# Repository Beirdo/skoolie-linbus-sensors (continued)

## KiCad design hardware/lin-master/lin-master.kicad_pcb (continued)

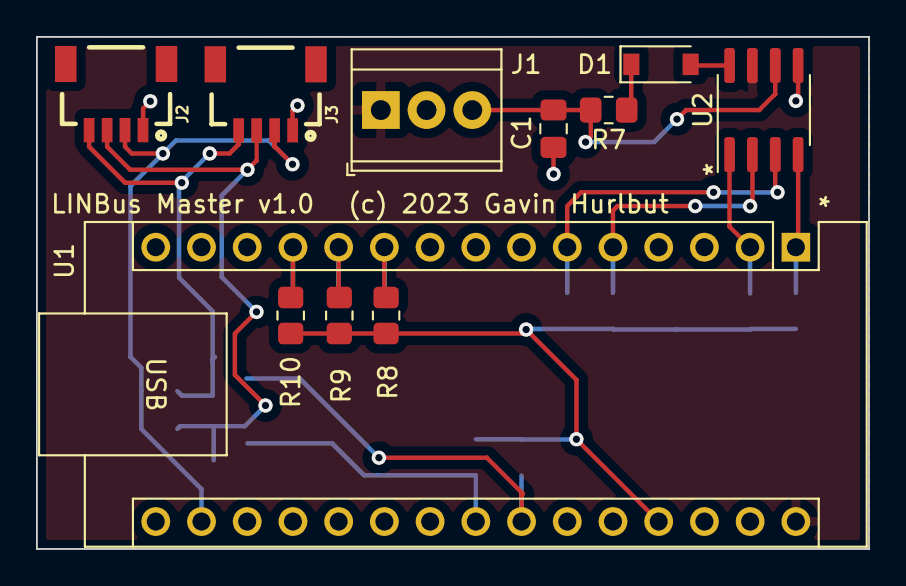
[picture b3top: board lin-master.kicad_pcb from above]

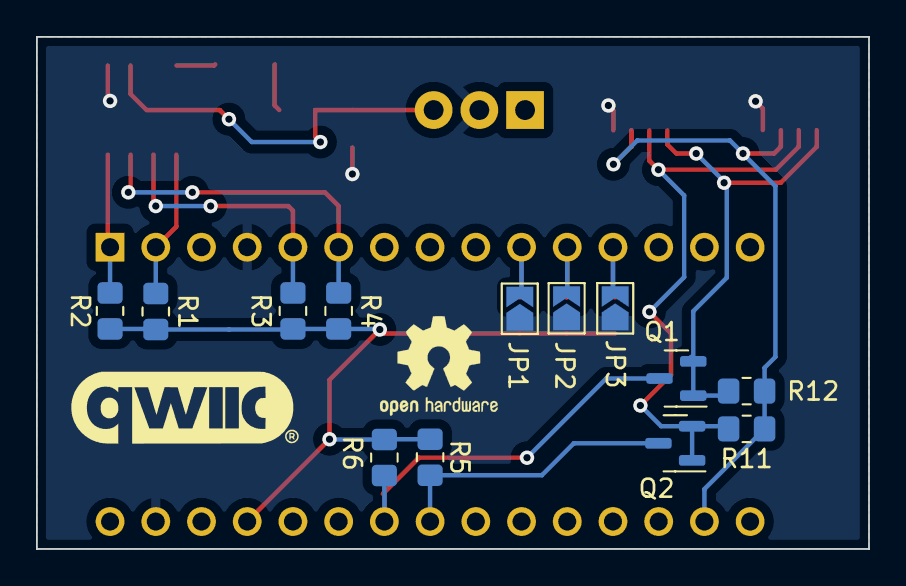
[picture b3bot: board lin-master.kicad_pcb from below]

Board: 2 copper layers, 46.2 x 28.4 mm, 24 parts (13 on the bottom side), 18 nets.

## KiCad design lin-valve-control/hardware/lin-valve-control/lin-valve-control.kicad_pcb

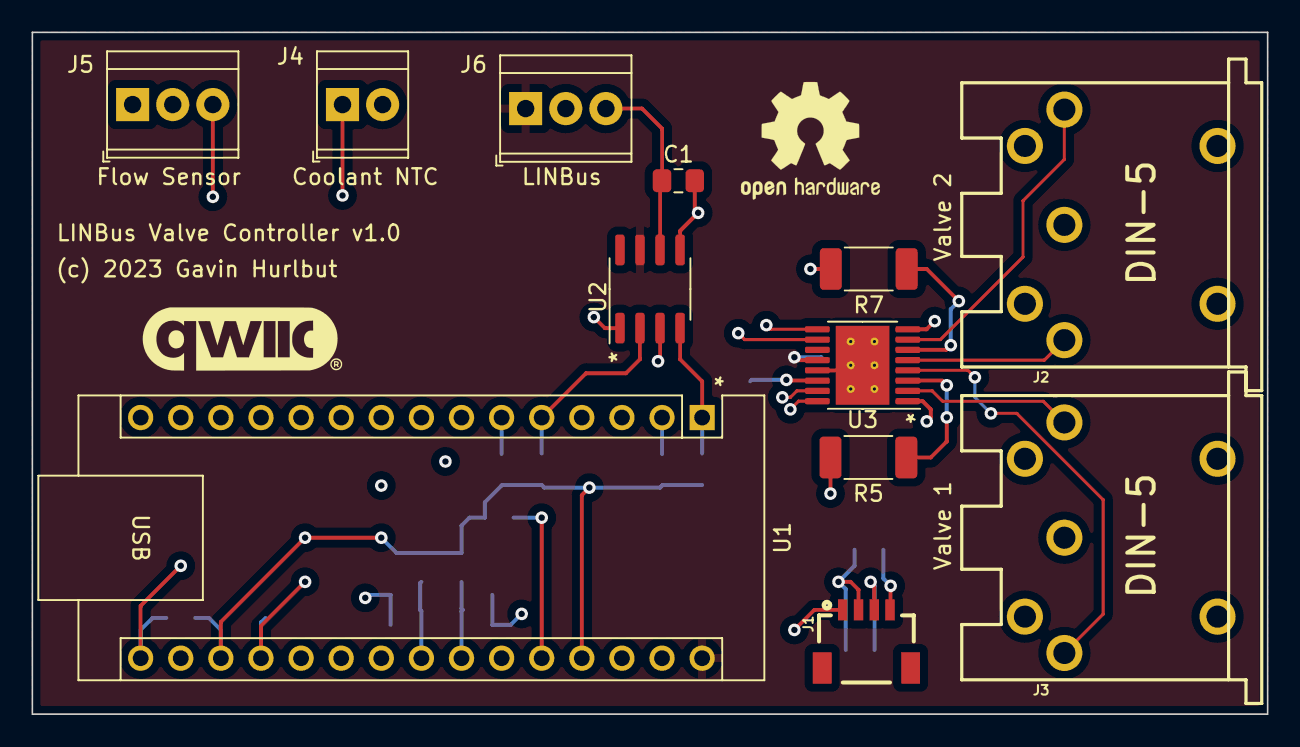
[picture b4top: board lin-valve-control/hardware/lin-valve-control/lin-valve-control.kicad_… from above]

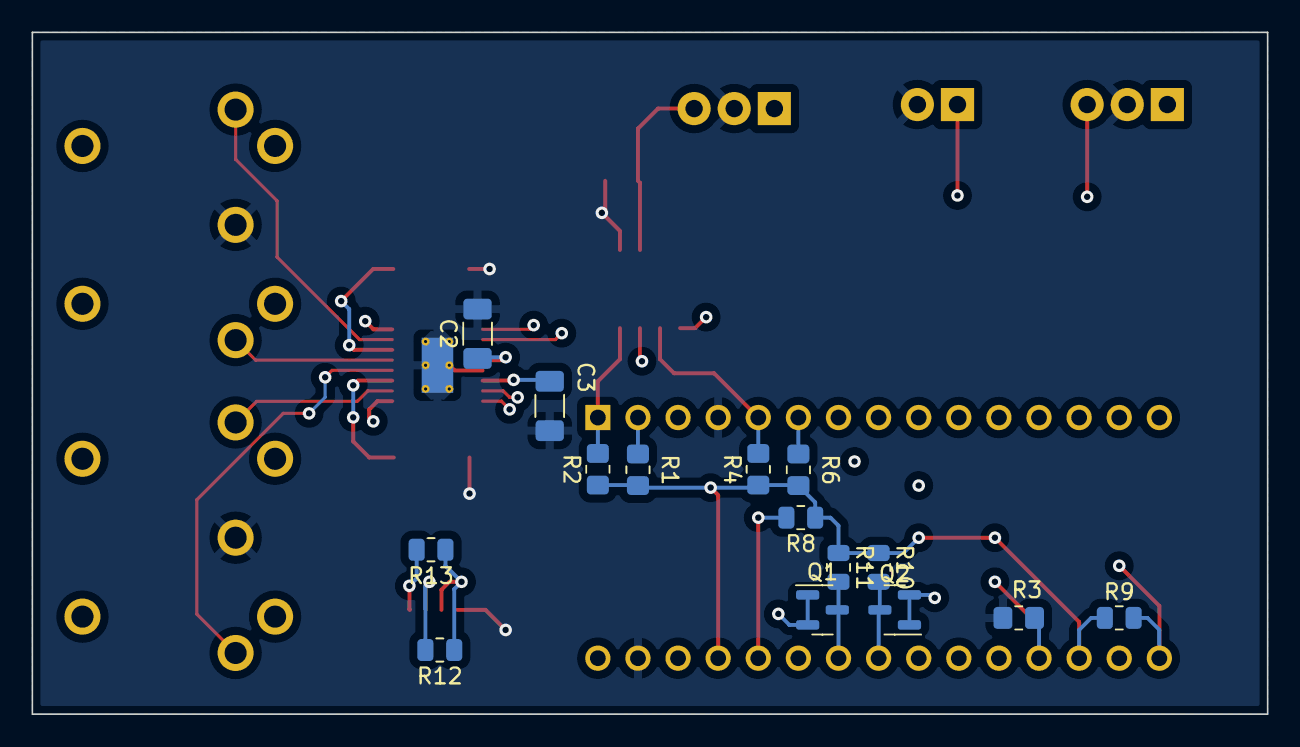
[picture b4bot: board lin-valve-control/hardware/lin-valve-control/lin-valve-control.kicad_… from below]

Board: 4 copper layers, 78.2 x 43.2 mm, 27 parts (15 on the bottom side), 32 nets.

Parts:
C1: 220pF; C_0805_2012Metric_Pad1.18x1.45mm_HandSolder
C2: 10uF 16V; C_1206_3216Metric_Pad1.33x1.80mm_HandSolder
C3: 2.2uF 6.3V; C_1206_3216Metric_Pad1.33x1.80mm_HandSolder
J1: QWIIC Connector; 1X04_1MM_RA
J2, J3: DIN-5_180degree; DIN5-RA-PTH
J4: Screw_Terminal_01x02; TerminalBlock_TE_282834-2_1x02_P2.54mm_Horizontal
J5, J6: Screw_Terminal_01x03; TerminalBlock_TE_282834-3_1x03_P2.54mm_Horizontal
Q1, Q2: 2N7002; SOT-23
R1, R2, R3, R4, R6: 10k; R_0805_2012Metric_Pad1.20x1.40mm_HandSolder
R5, R7: 2R 2W; R_2010_5025Metric_Pad1.40x2.65mm_HandSolder
R8, R9, R10, R11, R12, R13: 10k; R_0805_2012Metric
U1: Arduino_Nano_v3.x; Arduino_Nano
U2: TJA1021T; SOIC-8_3.9x4.9mm_P1.27mm
U3: DRV8833PWP; HTSSOP-16-1EP_4.4x5mm_P0.65mm_EP3.4x5mm_Mask2.46x2.31mm_The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

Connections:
+3V3: J1.2 (VCC), R12.1, R13.1, U1.17 (3V3)
+5V: J5.1, R1.1, R2.1, R4.1, R6.1, R8.1, R9.1, R10.1, R11.1, U1.18 (AREF), U1.27 (+5V)
+12V: C2.1, J6.1, U1.30 (VIN), U2.7 (VBAT), U3.12 (VM)
COOLANT_NTC: J4.1, R8.2, U1.26 (A7)
FLOW_PULSE: J5.3, U1.11 (D8)
GND: C1.2, C2.2, C3.2, J1.1 (GND), J2.2, J3.2, J4.2, J5.2, J6.2, R3.2, R5.2, R7.2, U1.4 (GND), U1.29 (GND), U2.5 (GND), U3.13 (GND), U3.17 (GND(PPAD))
LIN: C1.1, J6.3, U2.6 (LIN)
MOTOR_EN: R3.1, U1.19 (A0), U3.1 (nSLEEP)
unnamed: C3.1, U3.14 (VINT)
unnamed: R5.1, U3.3 (AISEN)
unnamed: R7.1, U3.6 (BISEN)
RXD: R1.2, U1.2 (D0/RX), U2.1 (RXD)
SCL: J1.4 (SCL), Q1.1 (G), Q1.2 (S), R13.2
SCL5: Q1.3 (D), R11.2, U1.24 (A5)
SDA: J1.3 (SDA), Q2.1 (G), Q2.2 (S), R12.2
SDA5: Q2.3 (D), R10.2, U1.23 (A4)
TXD: R2.2, U1.1 (D1/TX), U2.4 (TXD)
VALVE1+: J3.1, U3.2 (AOUT1)
VALVE1-: J3.3, U3.4 (AOUT2)
VALVE1_CLOSED: J3.5, U1.9 (D6)
VALVE1_OPEN: J3.4, U1.10 (D7)
VALVE2+: J2.1, U3.7 (BOUT1)
VALVE2-: J2.3, U3.5 (BOUT2)
VALVE2_CLOSED: J2.5, U1.14 (D11)
VALVE2_OPEN: J2.4, U1.15 (D12)
VALVE_IN1+: U1.7 (D4), U3.16 (AIN1)
VALVE_IN1-: U1.8 (D5), U3.15 (AIN2)
VALVE_IN2+: U1.12 (D9), U3.9 (BIN1)
VALVE_IN2-: U1.13 (D10), U3.10 (BIN2)
~LIN_SLP: R4.2, U1.5 (D2), U2.2 (~SLP)
~LIN_WAKE: R6.2, U1.6 (D3), U2.3 (~WAKE)
~MOTOR_FAULT: R9.2, U1.16 (D13), U3.8 (nFAULT)

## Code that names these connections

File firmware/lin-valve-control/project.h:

#ifndef __project_h_
#define __project_h_

#include <Arduino.h>
#include <Beirdo-Utilities.h>
#include <TCA9534-GPIO.h>

#define PIN_SCL           PIN_PB0
#define PIN_SDA           PIN_PB1
#define PIN_TXD           PIN_PB2
#define PIN_RXD           PIN_PB3
#define PIN_UPDI          PIN_PA0
#define PIN_VPROPI        PIN_PA1
#define PIN_I2C_INT       PIN_PA2
#define PIN_RESET         PIN_PA3
#define PIN_PHASE_PWM     PIN_PA4
#define PIN_LIN_SLP       PIN_PA5
#define PIN_LIN_WAKE      PIN_PA6
#define PIN_LED           PIN_PA7

// On the TCA9534
#define PIN_ENABLE        0
#define PIN_SLEEP         1
#define PIN_VALVE_CLOSED  4
#define PIN_VALVE_OPENED  5
#define PIN_FAULT         6

#define VALVE_CLOSED      BIT(3)
#define VALVE_OPENED      BIT(2)
#define VALVE_CLOSE       BIT(1)
#define VALVE_OPEN        BIT(0)

#define I2C_ADDR0_LCD     0x27
#define I2C_ADDR1_LCD     0x3F
#define I2C_ADDR_TCA9534  0x20

void setPhasePWM(bool cw, bool ccw);

extern TCA9534 tca9534;

#endif

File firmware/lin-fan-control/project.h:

#ifndef __project_h_
#define __project_h_

#include <Arduino.h>
#include <Beirdo-Utilities.h>

#define PIN_SCL           PIN_PB0
#define PIN_SDA           PIN_PB1
#define PIN_TXD           PIN_PB2
#define PIN_RXD           PIN_PB3
#define PIN_UPDI          PIN_PA0
#define PIN_ALERT         PIN_PA1
#define PIN_TCRIT         PIN_PA2
#define PIN_RESET         PIN_PA3
#define PIN_LIN_SLP       PIN_PA4
#define PIN_LIN_WAKE      PIN_PA5
#define PIN_LED           PIN_PA7

#endif

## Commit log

2023-02-04 Import some old stuff before its lost
2023-02-04 Redo the valve controller using an Arduino Nano
2023-02-04 Added LINBus Master schematic/layout
2023-02-04 Move flow sensor to ICP1, run it at 5V
2023-02-04 Move the hardware designs under hardware/
2023-02-05 Added firmware v1 for the valve-control board
2023-02-05 Add library
2023-02-05 Added I2C Addr lines and level translation
2023-02-06 Added firmware for lin-master
    - also added I2C address selection, and built-in 3.3V->5V translation
    and a second QWIIC connector.
2023-02-10 Added pins to control the cooling fan and the cooling pump
2023-02-10 Plumbed in the PWM Fan control and pump control
2023-02-10 Put in the Coolant Pump and Cooling Fan bits
2023-02-10 Sigh. forgot to save.
2023-02-15 Splitting into multiple pages.
2023-02-15 Update lin-master firmware and valve control board
2023-02-15 Updated valve controller board
2023-02-15 Add a connector to attach 20x4 LCD on an I2C backpack
2023-02-15 Regenerate schematic PDF
2023-02-15 Seems I have to *plot* this schematic, not print.
    - if I use print, it will only do either the title block OR the
    circuitry, but if I plot it works.
2023-02-17 Change to A4 size paper
2023-02-17 Completely redo the valve controller. One valve only.
2023-02-17 Uptdate title block
2023-02-17 Update firmware readme
2023-02-17 Add PCA9536 for the LINBus Address
2023-02-18 Get this in place (barely) on ATTiny824.
    - should not be THAT big, I thought. Investigation to follow:
    Sketch uses 7998 bytes (97%) of program storage space. Maximum is 8192 bytes.
2023-02-18 Make things less dynamic
    Sketch uses 7687 bytes (93%) of program storage space. Maximum is 8192 bytes.
2023-02-18 Board design for coolant temperature thermistors.
2023-02-18 Add firmware for lin-coolant-temperature, cleanup layout
2023-02-18 Add lin-flow-sensor hardware and preliminary firmware
2023-02-19 Add fan control hardware design.
    - control one fan with 2, 3 or 4 pin connectivity, providing PWM and tach support for all.
    - one remote PN-junction temperature probe (will put in the outbound air flow)
2023-02-19 Adding shell firmware forthe fan control
2023-02-19 Started mapping out registers
2023-02-20 AddingLM96163 support
2023-02-20 Add the pump controller
2023-02-20 Tweaks to clean up a bit.
2023-02-20 Add Peltier controller (14A fuse rather than 6A)
2023-02-20 Added peltier controller code
    - need to consider splitting out common code to a library?
2023-02-21 Tweak the master to follow changes in LINBUS/-stack
2023-02-21 Added the location register. This propagates to the master on enumeration
2023-02-25 Moved git KiCad libs to new repo
    - https://github.com/Beirdo/KiCad-Git-Libraries
2023-02-27 Oops, typo
2023-03-02 Remove old linbus-master design
2023-03-02 Add INA219 to pump controller, change to using regulator module
2023-03-02 Update the peltier controller to include INA219.
    - resistor value to be changed in a bit.
2023-03-03 Convert the peltier controller firmware
2023-03-03 Rework valve-controller board, simplify firmware
    - linbus_interface and linbus_registers moved to the common lib.
    - reworked them all to compile again
    - removing PCA9536 from all boards, adding the voltage reg. module
2023-03-04 Update the schematics... remove PCA9536, use voltage regulator
2023-03-05 Moved linbus-coolant-temperature over to PlatformIO
2023-03-05 Moved linbus-fan-control to PlatformIO
2023-03-05 Moved linbus-flow-sensor to PlatformIO
2023-03-05 Moved lin-peltier-control to PlatformIO
2023-03-05 Moved lin-pump-control to PlatformIO
2023-03-05 Moves lin-valve-control to PlatformIO
2023-03-06 Move away from .ino
2023-03-07 Moved lin-coolant-temperature to lib_deps
2023-03-07 Changed lin-fan-control to lib_deps
2023-03-07 Moved lin-flow-sensor to lib_deps
2023-03-07 Moved lin-peltier-control to lib_deps
2023-03-07 Moved lin-pump-control to lib_deps
2023-03-07 Moved lin-valve-control to lib_defs
